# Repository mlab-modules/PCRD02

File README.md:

# PCRD - Plocs Cosmic Ray Detector

The PCRD is a semiconductor detector for cosmic rays. Its main advantages include sensitivity to all charged particles, low energy consumption, and low weight. Additionally, if the interaction with radiation transfers all its energy to the silicon, it is possible to determine the energy spectrum of the mixed radiation field.

## Technical Parameters

| **Parameter** | **Value**           | **Note**                 |
|---------------|---------------------|--------------------------|
| Power Supply  | +/- 2.4V            |                          |
| Dimensions    | 30.0 x 50.3 x 16 mm | Height above base board  |

## Construction Description

### Mechanical Construction

The module contains mounting screws in all corners with an MLAB pitch (10.16mm). If space-saving is needed, the part of the PCB with two screws can be broken off.

## Assembly and Commissioning

### Assembly

| **Designation** | **Type**   | **Package**                | **Quantity** |
|-----------------|------------|----------------------------|--------------|
| R7              | 2M         | SMD-0805                   | 1            |
| C1, C2          | 100nF      | SMD-0805                   | 2            |
| C3, C4, C9, C10, C11 | 100n | SMD-0805                   | 5            |
| C13, C17        | 330nF      | SMD-0805                   | 2            |
| C14             | 510pF      | SMD-0805                   | 1            |
| C15             | 220pF      | SMD-0805                   | 1            |
| C16             | 150pF      | SMD-0805                   | 1            |
| J2              | JUMP_3X2   | Pin_Header_Straight_2x03   | 1            |
| J3              | JUMP_5X2   | Pin_Header_Straight_2x05   | 1            |
| J4              | Out        | Pin_Header_Straight_2x03   | 1            |
| P1, P2, P3, P4  | _          | MountingHole_3mm           | 4            |
| Q1              | BF862      | SOT-23                     | 1            |
| R1, R2          | 4M7        | SMD-0805                   | 2            |
| R8              | 3k3        | SMD-0805                   | 1            |
| R9, R15         | 10k        | SMD-0805                   | 2            |
| R10             | 1k5        | SMD-0805                   | 1            |
| R11             | 6k2        | SMD-0805                   | 1            |
| R12, R13, R14   | 2k41k      | SMD-0805                   | 3            |
| U1              | AD8691     | tsot-5                     | 1            |
| J1              | CONN1_2    | CONN_3_2                   | 1            |
| U2              | AD8692     | SOIC-8-N                   | 1            |
| C5, C8          | 2pF        | 2pF_PCB                    | 2            |
| **Variant 1**   |            |                            |              |
| R3              | 1k         | SMD-0805                   | 1            |
| R4              | 62         | SMD-0805                   | 1            |
| R5              | 100        | SMD-0805                   | 1            |
| R6              | 2k         | SMD-0805                   | 1            |
| **Variant 2**   |            |                            |              |
| R3              | 1k         | SMD-0805                   | 1            |
| R4              | 300        | SMD-0805                   | 1            |
| R5              | 430        | SMD-0805                   | 1            |
| R6              | 1k         | SMD-0805                   | 1            |

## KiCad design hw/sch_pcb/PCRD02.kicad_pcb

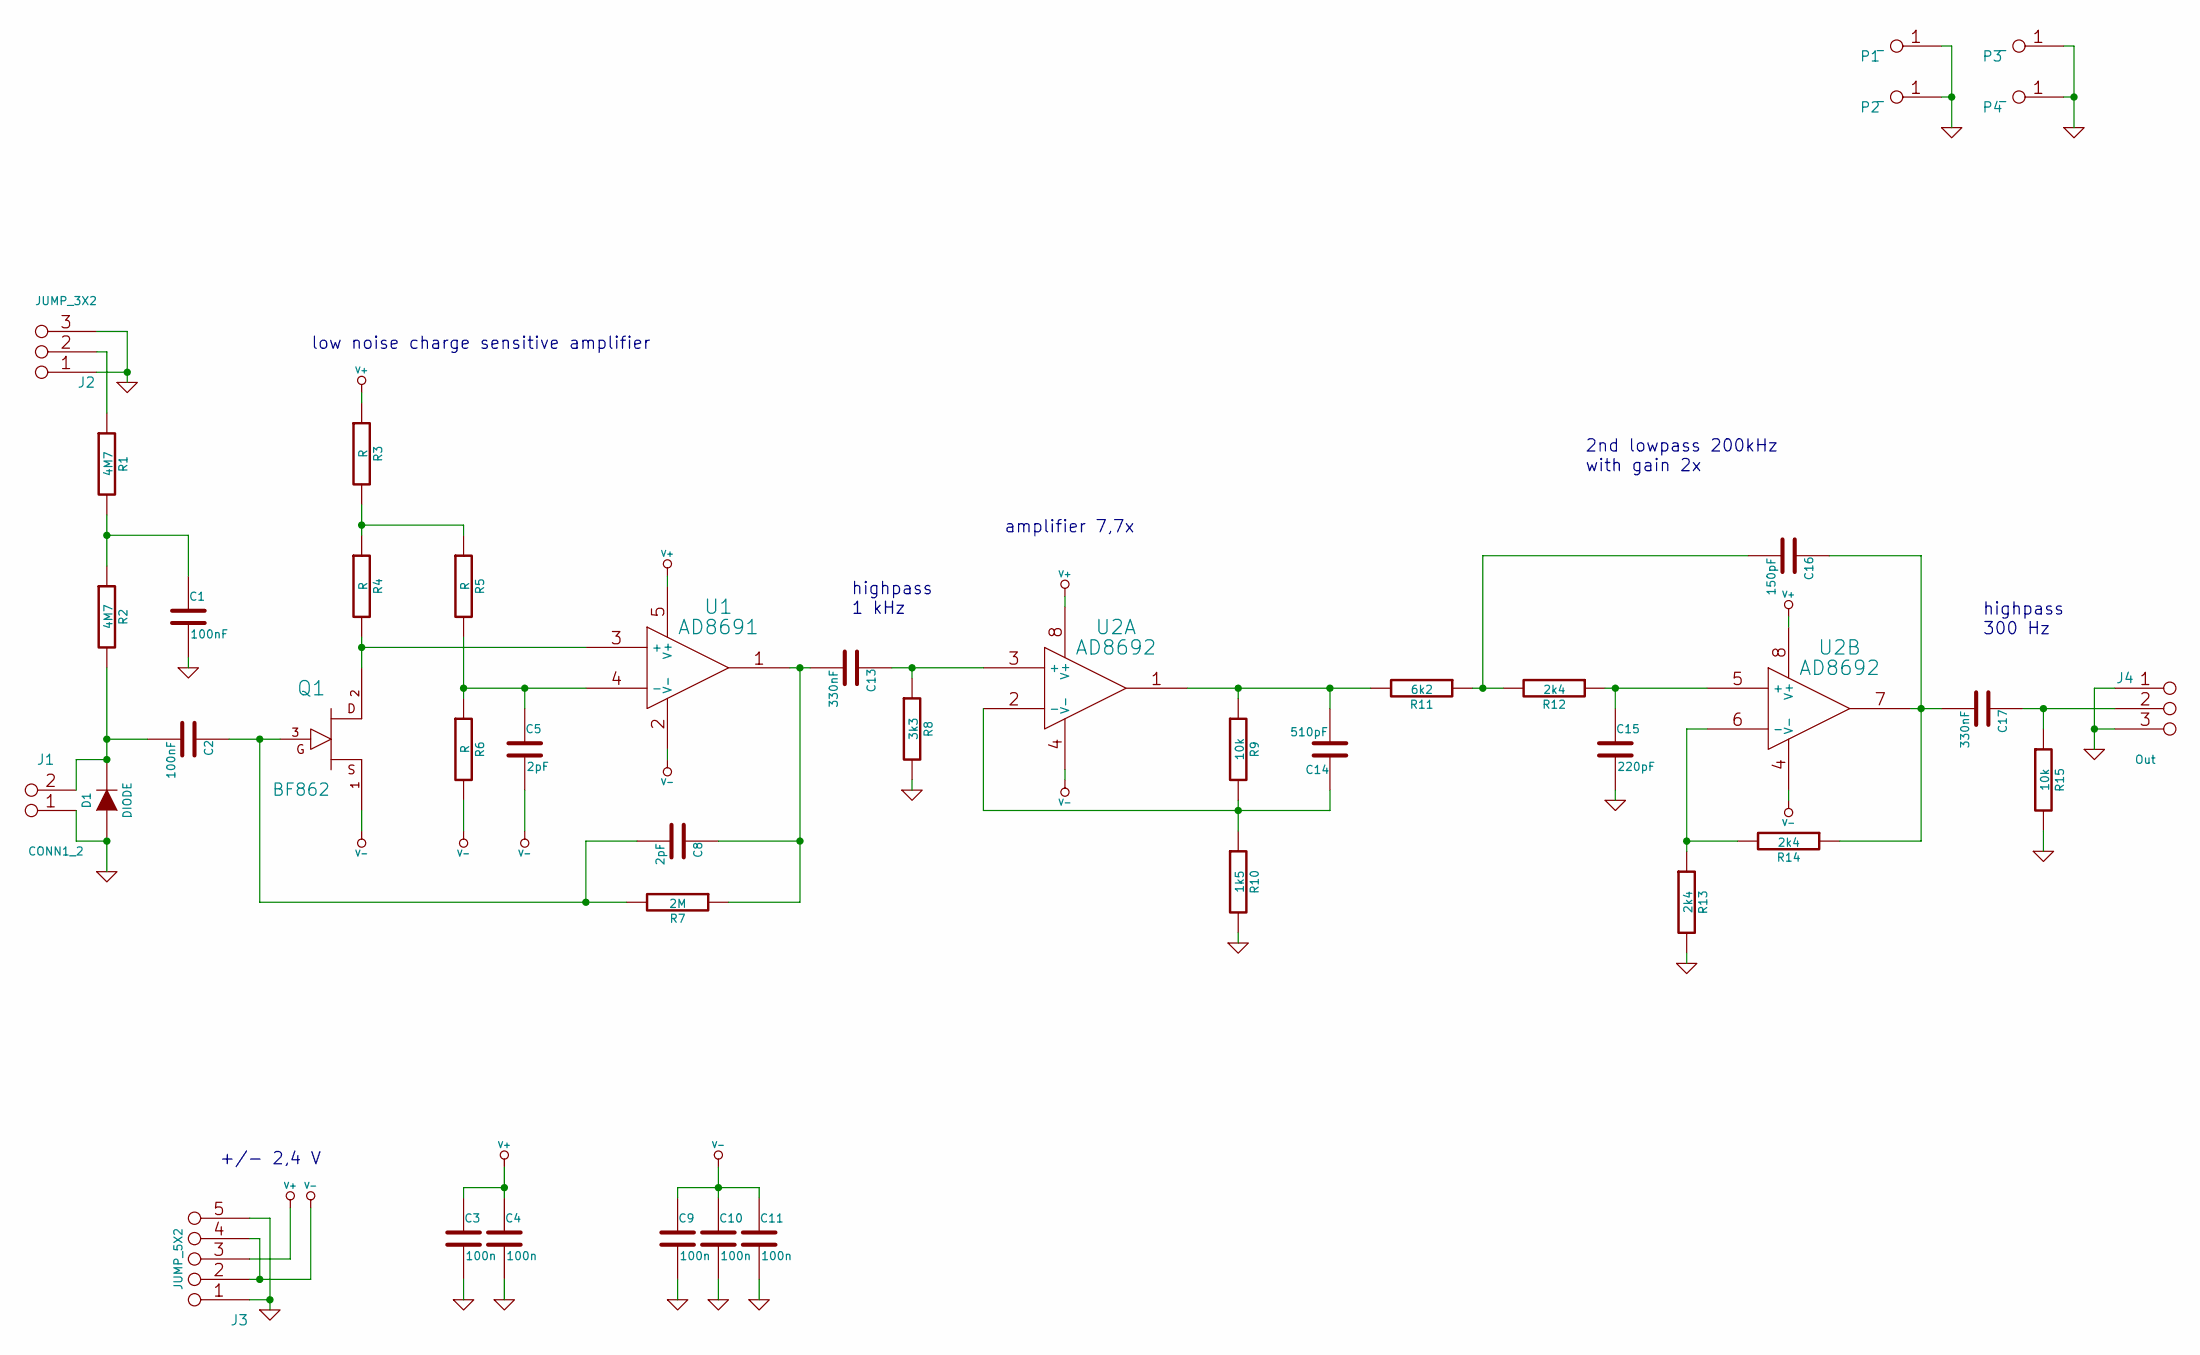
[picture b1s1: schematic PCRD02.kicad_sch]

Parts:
C1, C2: 100nF; SMD-0805
C3, C4, C9, C10, C11: 100n; SMD-0805
C5, C8: 2pF; C2pF
C13, C17: 330nF; SMD-0805
C14: 510pF; SMD-0805
C15: 220pF; SMD-0805
C16: 150pF; SMD-0805
D1: DIODE
J1: CONN1_2; CONN_3_2
J2: JUMP_3X2; Pin_Header_Straight_2x03
J3: JUMP_5X2; Pin_Header_Straight_2x05
J4: Out; Pin_Header_Straight_2x03
P1, P2, P3, P4: _; MountingHole_3mm
Q1: BF862; SOT-23
R1, R2: 4M7; SMD-0805
R3, R4, R5, R6: R; SMD-0805
R7: 2M; SMD-0805
R8: 3k3; SMD-0805
R9, R15: 10k; SMD-0805
R10: 1k5; SMD-0805
R11: 6k2; SMD-0805
R12, R13, R14: 2k4; SMD-0805
U1: AD8691; tsot-5
U2: AD8692; SOIC-8-N

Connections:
GND: C1.2, C3.2, C4.2, C9.2, C10.2, C11.2, C15.2, D1.1 (A), J1.1, J2.1, J2.3, J2.4, J2.6, J3.1, J3.5, J3.6, J3.10, J4.1, J4.3, J4.4, J4.6, P1.1, P2.1, P3.1, P4.1, R8.2, R10.2, R13.2, R15.2
unnamed: C1.1, R1.2, R2.1
unnamed: C2.1, C8.2, Q1.3 (G), R7.2
unnamed: C2.2, D1.2 (K), J1.2 (PM), R2.2
unnamed: C5.1, R5.2, R6.1, U1.4 (-)
unnamed: C13.1, R8.1, U2.3 (+)
unnamed: C8.1, C13.2, R7.1, U1.1
unnamed: C14.1, R9.2, R10.1, U2.2 (-)
unnamed: C14.2, R9.1, R11.2, U2.1
unnamed: C15.1, R12.1, U2.5 (+)
unnamed: C16.1, C17.2, R14.1, U2.7
unnamed: C16.2, R11.1, R12.2
unnamed: C17.1, J4.2 (1), J4.5, R15.1
unnamed: J2.2 (1), J2.5, R1.1
unnamed: Q1.2 (D), R4.2, U1.3 (+)
unnamed: R3.2, R4.1, R5.1
unnamed: R13.1, R14.2, U2.6 (-)
V+: C3.1, C4.1, J3.3, J3.8, R3.1, U1.5 (V+), U2.8 (V+)
V-: C5.2, C9.1, C10.1, C11.1, J3.2, J3.4, J3.7, J3.9, Q1.1 (S), R6.2, U1.2 (V-), U2.4 (V-)

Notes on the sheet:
2nd lowpass 200kHz with gain 2x
amplifier 7,7x
highpass 300 Hz
+/- 2,4 V
low noise charge sensitive amplifier
highpass 1 kHz

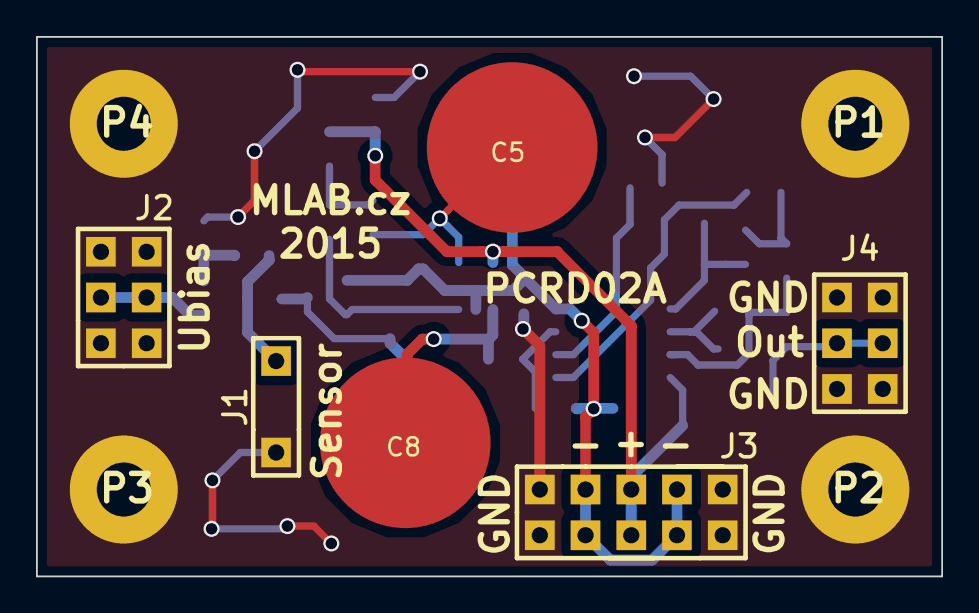
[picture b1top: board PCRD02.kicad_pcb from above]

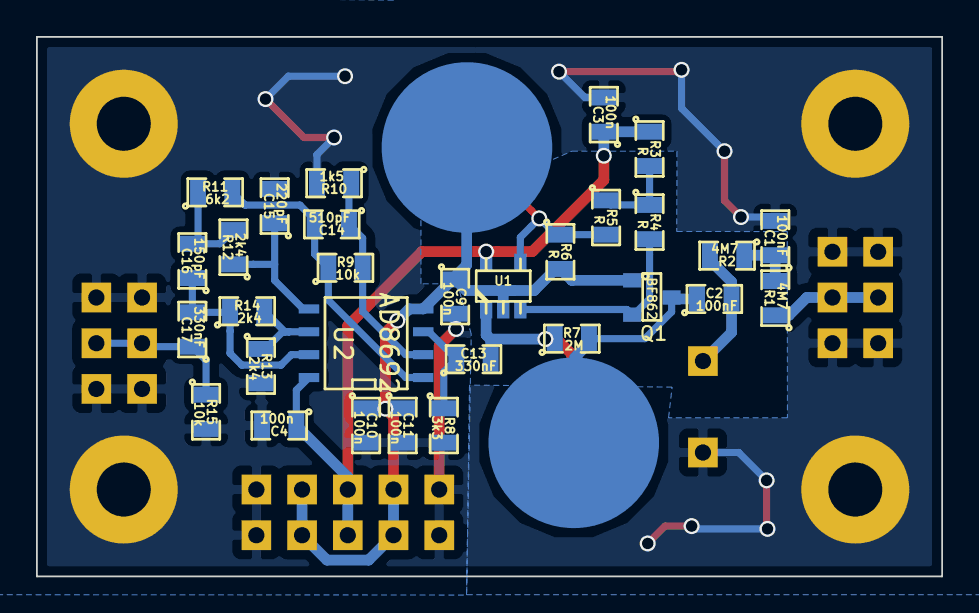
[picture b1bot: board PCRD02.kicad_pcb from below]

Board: 2 copper layers, 50.3 x 30.0 mm, 40 parts (30 on the bottom side), 19 nets.

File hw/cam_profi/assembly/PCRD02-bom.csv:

Component,Description,Part,References,Value,Footprint,Quantity Per PCB,Datasheet
1,,C,C5C8,2pF,C2pF,2,
2,,C,C16,150pF,SMD-0805,1,
3,,C,C15,220pF,SMD-0805,1,
4,,C,C14,510pF,SMD-0805,1,
5,,C,C1C2C3C4C9C10C11,100nF,SMD-0805,7,
6,,C,C13C17,330nF,SMD-0805,2,
7,,DIODE,D1,DIODE,,1,
8,,CONN1_2,J1,CONN1_2,CONN_3_2,1,
9,,JUMP_3X2,J2,JUMP_3X2,Pin_Header_Straight_2x03,1,
10,,JUMP_5X2,J3,JUMP_5X2,Pin_Header_Straight_2x05,1,
11,,JUMP_3X2,J4,Out,Pin_Header_Straight_2x03,1,
12,,JFET_N,Q1,BF862,SOT-23,1,
13,,R,R10,1k5,SMD-0805,1,
14,,R,R12R13R14,2k4,SMD-0805,3,
15,,R,R8,3k3,SMD-0805,1,
16,,R,R11,6k2,SMD-0805,1,
17,,R,R9R15,10k,SMD-0805,2,
18,,R,R7,2M,SMD-0805,1,
19,,R,R1R2,4M7,SMD-0805,2,
20,,R,R3R4R5R6,R,SMD-0805,4,
21,,AD8691,U1,AD8691,tsot-5,1,
22,,AD8692,U2,AD8692,SOIC-8-N,1,

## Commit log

2017-08-24 Microcontrollers and processors moved to separate directory.
2018-02-15 [MLABweb] 2018-02-15 20:37:09 PCRD02A
2018-02-26 [MLABweb] 2018-02-26 00:33:43 PCRD02A
2018-04-12 [MLABweb] Documentaion edits; PCRD02A
2018-11-05 Presun obrazku do slozky img. Pregenerovani dokumentaci.
2020-11-04 Fix license
2022-04-06 automated commit; add github actions
2022-04-06 Update actions products
2023-02-14 update actions
2023-02-14 Update metadata files
2023-07-05 automated commit; rename source files to new naming convence
2023-09-16 Update status
2024-07-03 Update project names.
2024-07-03 Update project to KiCADv7, crop the title image.
2024-07-04 Update workflow files
